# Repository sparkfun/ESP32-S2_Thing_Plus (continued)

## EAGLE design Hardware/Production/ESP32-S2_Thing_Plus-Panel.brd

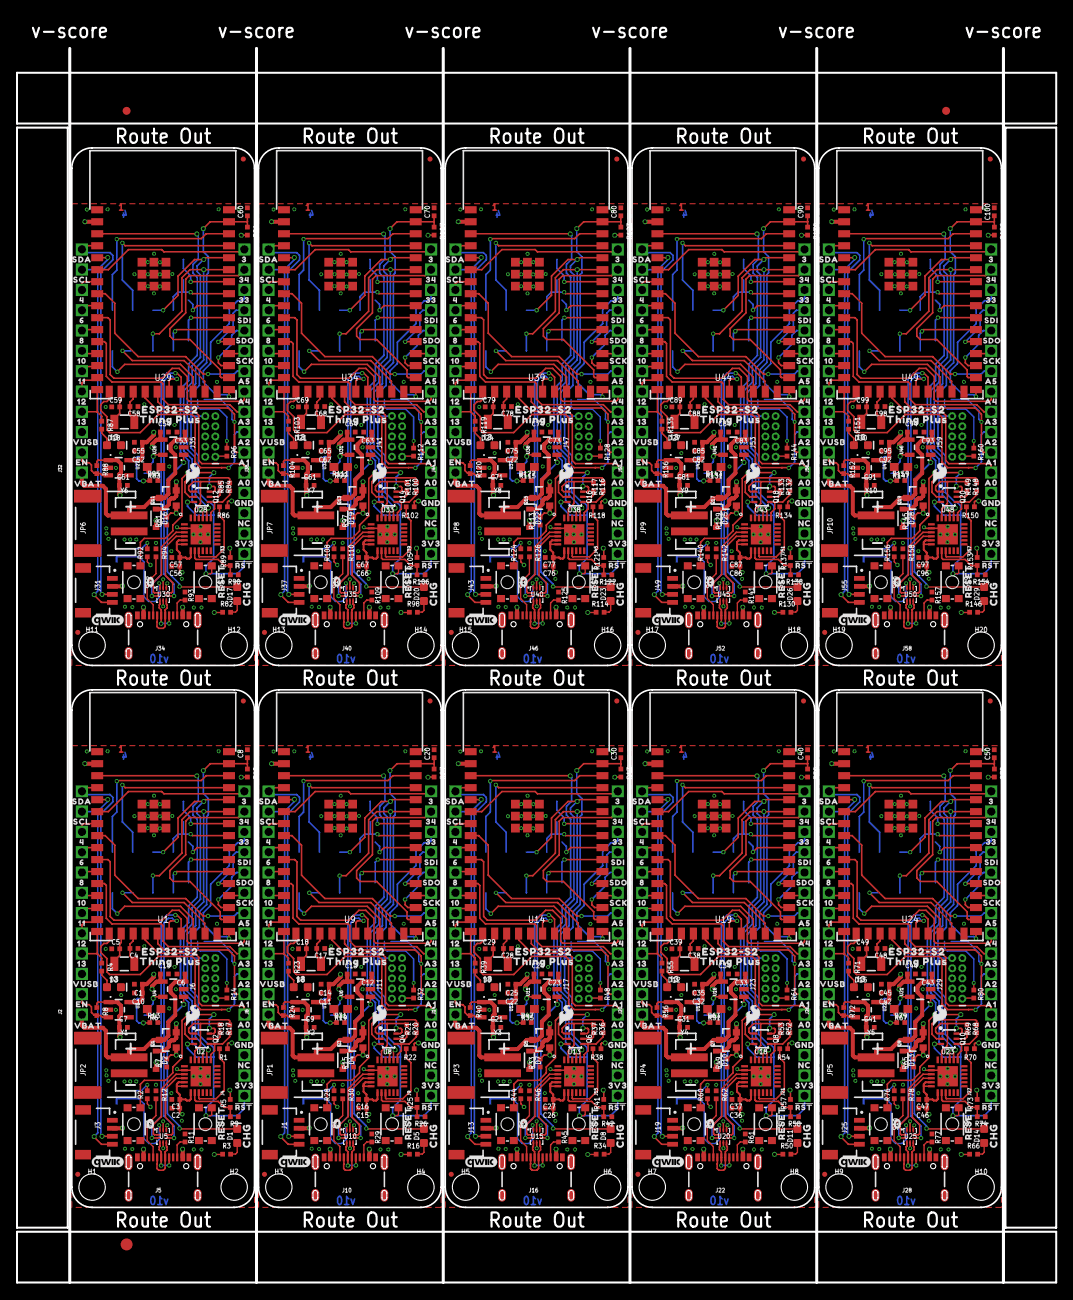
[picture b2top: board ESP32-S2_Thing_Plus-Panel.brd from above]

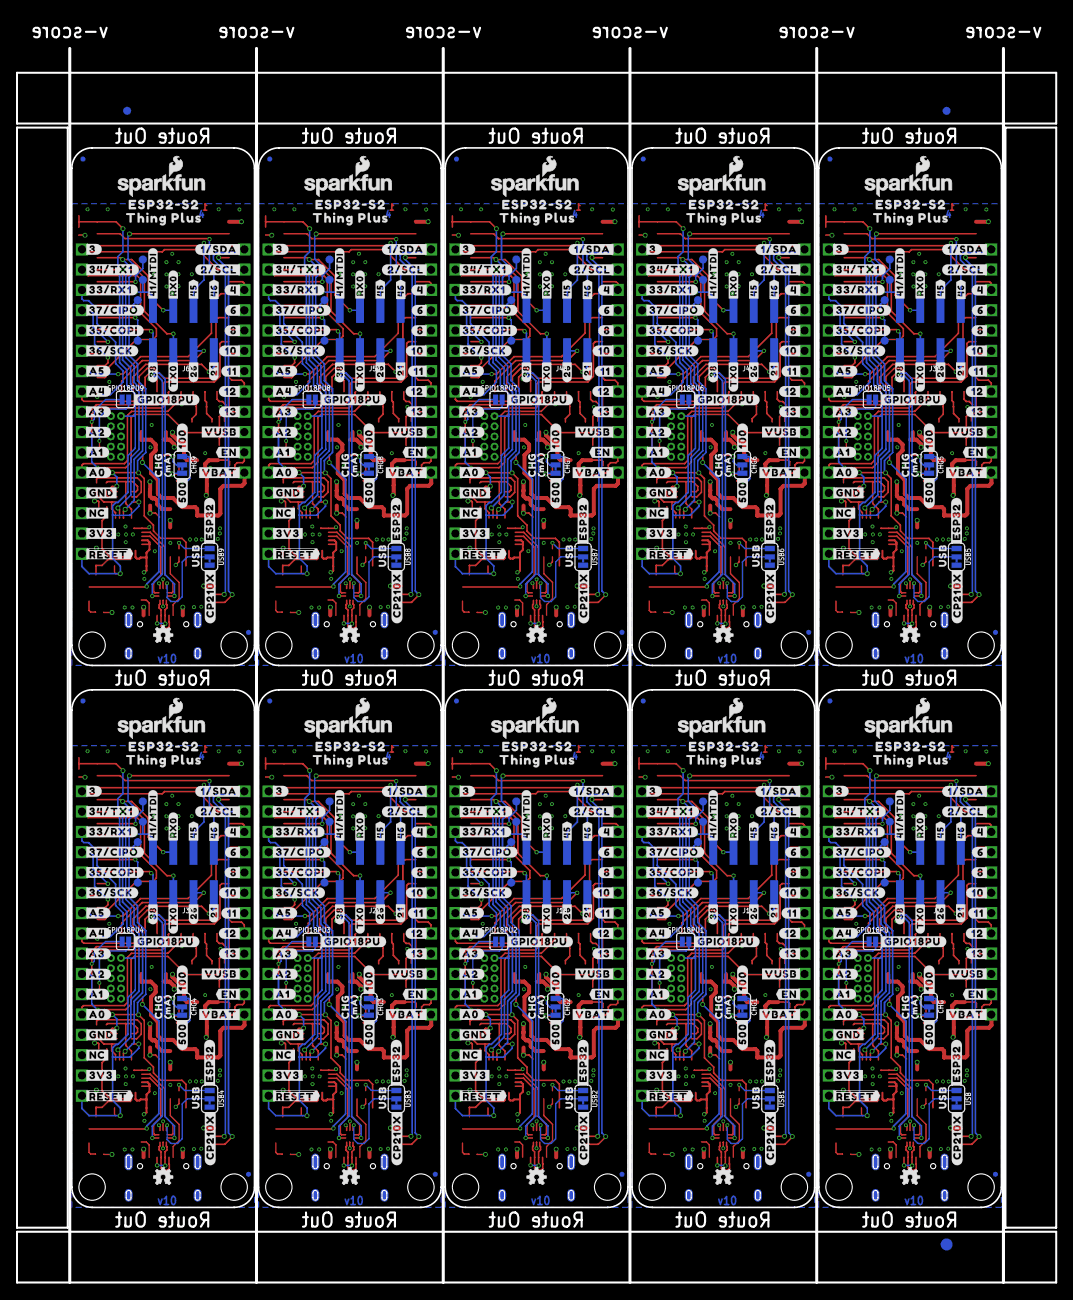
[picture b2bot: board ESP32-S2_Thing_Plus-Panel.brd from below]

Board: 4 copper layers, 130.0 x 154.4 mm, 1466 parts (583 on the bottom side), 650 nets.

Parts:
C1, C14, C25, C35, C45, C55, C65, C75, C85, C95: 10uF; 0402-TIGHT
C2, C8, C15, C20, C26, C30, C36, C40, C46, C50, C56, C60, C66, C70, C76, C80, C86, C90, C96, C100: 0.1uF; 0402-TIGHT
C3, C6, C12, C13, C16, C19, C23, C24, C27, C33, C34, C37, C43, C44, C47, C53, C54, C57, C63, C64, C67, C73, C74, C77, C83, C84, C87, C93, C94, C97: 4.7uF; 0402-TIGHT
C4, C5, C17, C18, C28, C29, C38, C39, C48, C49, C58, C59, C68, C69, C78, C79, C88, C89, C98, C99: 15pF; 0402-TIGHT
C7, C9, C10, C11, C21, C22, C31, C32, C41, C42, C51, C52, C61, C62, C71, C72, C81, C82, C91, C92: 1.0uF; 0402-TIGHT
CHG, CHG1, CHG2, CHG3, CHG4, CHG5, CHG6, CHG7, CHG8, CHG9: SMT-JUMPER_3_1-NC_TRACE_SILK
D1, D5, D8, D11, D14, D17, D20, D23, D26, D29: Yellow; LED-0603
D2, D4, D7, D10, D13, D16, D19, D22, D25, D28: 1A/23V/620mV; SOD-323
D3, D6, D9, D12, D15, D18, D21, D24, D27, D30: BLUE; LED-0603
E$1, E$2, E$3, E$4: FIDUCIAL-1X2
E$5, E$6: FIDUCIAL-1.5X3
FD1, FD2, FD3, FD4, FD5, FD6, FD7, FD8, FD9, FD10, FD11, FD12, FD13, FD14, FD15, FD16, FD17, FD18, FD19, FD20, FD21, FD22, FD23, FD24, FD25, FD26, FD27, FD28, FD29, FD30, FD31, FD32, FD33, FD34, FD35, FD36, FD37, FD38, FD39, FD40: FIDUCIALUFIDUCIAL; FIDUCIAL-MICRO
GPIO18PU, GPIO18PU1, GPIO18PU2, GPIO18PU3, GPIO18PU4, GPIO18PU5, GPIO18PU6, GPIO18PU7, GPIO18PU8, GPIO18PU9: SMT-JUMPER_2_NO_SILK
H1, H2, H3, H4, H5, H6, H7, H8, H9, H10, H11, H12, H13, H14, H15, H16, H17, H18, H19, H20: STAND-OFF
J1, J3, J13, J19, J25, J31, J37, J43, J49, J55: QWIIC_RA; JST04_1MM_RA
J2, J8, J14, J20, J26, J32, J38, J44, J50, J56: 1X12_SM_SQ_NOSILK
J4, J9, J15, J21, J27, J33, J39, J45, J51, J57: 1X16_SM_SQ_NOSILK
J5, J10, J16, J22, J28, J34, J40, J46, J52, J58: USB-C; USB-C-16P-4LAYER-ISOLATED
J6, J11, J17, J23, J29, J35, J41, J47, J53, J59: JTAG; 2X5-PTH-1.27MM-NO_SILK
J7, J12, J18, J24, J30, J36, J42, J48, J54, J60: 2X4_SMT_NO_POSTS_NS
JP1, JP2, JP3, JP4, JP5, JP6, JP7, JP8, JP9, JP10: LiPo; JST-2-SMD
LOGO1, LOGO10, LOGO15, LOGO20, LOGO25, LOGO30, LOGO35, LOGO40, LOGO45, LOGO50: SFE_LOGO_FLAME.1_INCH; SFE_LOGO_FLAME_.1
LOGO2, LOGO5, LOGO11, LOGO16, LOGO21, LOGO26, LOGO31, LOGO36, LOGO41, LOGO46: OSHW-LOGOMINI; OSHW-LOGO-MINI
LOGO3, LOGO7, LOGO12, LOGO17, LOGO22, LOGO27, LOGO32, LOGO37, LOGO42, LOGO47: SFE_LOGO_NAME_FLAME.1_INCH; SFE_LOGO_NAME_FLAME_.1
LOGO4, LOGO8, LOGO13, LOGO18, LOGO23, LOGO28, LOGO33, LOGO38, LOGO43, LOGO48: FOUR_LAYER_WARNING
LOGO6, LOGO9, LOGO14, LOGO19, LOGO24, LOGO29, LOGO34, LOGO39, LOGO44, LOGO49: QWIIC_LOGO_4MM; QWIIC_4MM
Q1, Q3, Q5, Q7, Q9, Q11, Q13, Q15, Q17, Q19: 2.5A/30V; SOT23-3@1
Q2, Q4, Q6, Q8, Q10, Q12, Q14, Q16, Q18, Q20: MBT3904DW1T1; SC70-6
R1, R2, R7, R10, R13, R14, R15, R17, R18, R20, R21, R22, R27, R28, R31, R32, R33, R36, R37, R38, R43, R44, R47, R48, R49, R52, R53, R54, R59, R60, R63, R64, R65, R68, R69, R70, R75, R76, R79, R80, R81, R84, R85, R86, R91, R92, R95, R96, R97, R100, R101, R102, R107, R108, R111, R112, R113, R116, R117, R118, R123, R124, R127, R128, R129, R132, R133, R134, R139, R140, R143, R144, R145, R148, R149, R150, R155, R156, R159, R160: 10k; 0402-TIGHT
R3, R4, R16, R23, R34, R39, R50, R55, R66, R71, R82, R87, R98, R103, R114, R119, R130, R135, R146, R151: 1k; 0402-TIGHT
R5, R25, R41, R57, R73, R89, R105, R121, R137, R153: 22k; 0402-TIGHT
R6, R19, R35, R51, R67, R83, R99, R115, R131, R147: 2.0k; 0603
R8, R24, R40, R56, R72, R88, R104, R120, R136, R152: 100k; 0402-TIGHT
R9, R26, R42, R58, R74, R90, R106, R122, R138, R154: 33k; 0402-TIGHT
R11, R12, R29, R30, R45, R46, R61, R62, R77, R78, R93, R94, R109, R110, R125, R126, R141, R142, R157, R158: 5.1k; 0402-TIGHT
S1, S3, S5, S7, S9, S11, S13, S15, S17, S19: RESET; TACTILE_SWITCH_SMD_4.6X2.8MM
S2, S4, S6, S8, S10, S12, S14, S16, S18, S20: 0; TACTILE_SWITCH_SMD_4.6X2.8MM
TP1, TP6, TP11, TP16, TP21, TP26, TP31, TP36, TP41, TP46: TP_15TH
TP2, TP3, TP4, TP5, TP7, TP8, TP9, TP10, TP12, TP13, TP14, TP15, TP17, TP18, TP19, TP20, TP22, TP23, TP24, TP25, TP27, TP28, TP29, TP30, TP32, TP33, TP34, TP35, TP37, TP38, TP39, TP40, TP42, TP43, TP44, TP45, TP47, TP48, TP49, TP50: PAD.03X.04
U1, U9, U14, U19, U24, U29, U34, U39, U44, U49: ESP32-S2-WROOM
U2, U8, U13, U18, U23, U28, U33, U38, U43, U48: CP210X; QFN24
U3, U7, U12, U17, U22, U27, U32, U37, U42, U47: AP2112; SOT23-5
U4, U6, U11, U16, U21, U26, U31, U36, U41, U46: MCP73831; SOT23-5
U5, U10, U15, U20, U25, U30, U35, U40, U45, U50: TC7USB40MU; UQFN10
U$1, U$160, U$241, U$322, U$403, U$484, U$565, U$646, U$727, U$808: #CP210X#0
U$2, U$116, U$197, U$278, U$359, U$440, U$521, U$602, U$683, U$764: SDI0
U$3, U$78, U$80, U$141, U$172, U$222, U$253, U$303, U$334, U$384, U$415, U$465, U$496, U$546, U$577, U$627, U$658, U$708, U$739, U$789: CHG0
U$4, U$152, U$233, U$314, U$395, U$476, U$557, U$638, U$719, U$800: #500#0
U$5, U$153, U$234, U$315, U$396, U$477, U$558, U$639, U$720, U$801: ESP32#S20
U$6, U$117, U$198, U$279, U$360, U$441, U$522, U$603, U$684, U$765: SDO0
U$7, U$118, U$199, U$280, U$361, U$442, U$523, U$604, U$685, U$766: #RST#0
U$8, U$142, U$223, U$304, U$385, U$466, U$547, U$628, U$709, U$790: #46#0
U$9, U$161, U$242, U$323, U$404, U$485, U$566, U$647, U$728, U$809: #ESP32#0
U$10, U$143, U$224, U$305, U$386, U$467, U$548, U$629, U$710, U$791: #45#0
U$11, U$150, U$231, U$312, U$393, U$474, U$555, U$636, U$717, U$798: MA0
U$12, U$109, U$190, U$271, U$352, U$433, U$514, U$595, U$676, U$757: #A5#0
U$13, U$59, U$163, U$244, U$325, U$406, U$487, U$568, U$649, U$730: ORDERING_INSTRUCTIONS
U$14, U$119, U$200, U$281, U$362, U$443, U$524, U$605, U$686, U$767: USB0
U$15, U$120, U$201, U$282, U$363, U$444, U$525, U$606, U$687, U$768: 110
U$16, U$162, U$243, U$324, U$405, U$486, U$567, U$648, U$729, U$810: #GPIO18PU#0
U$17, U$121, U$202, U$283, U$364, U$445, U$526, U$607, U$688, U$769: 100
U$18, U$122, U$203, U$284, U$365, U$446, U$527, U$608, U$689, U$770: 80
U$19, U$110, U$191, U$272, U$353, U$434, U$515, U$596, U$677, U$758: #A4#0
U$20, U$123, U$204, U$285, U$366, U$447, U$528, U$609, U$690, U$771: 60
U$21, U$158, U$239, U$320, U$401, U$482, U$563, U$644, U$725, U$806: #A2#0
U$22, U$159, U$240, U$321, U$402, U$483, U$564, U$645, U$726, U$807: #A3#0
U$23, U$124, U$205, U$286, U$367, U$448, U$529, U$610, U$691, U$772: 40
U$24, U$125, U$206, U$287, U$368, U$449, U$530, U$611, U$692, U$773: 330
U$25, U$27, U$164, U$245, U$326, U$407, U$488, U$569, U$650, U$731: SDA0
U$26, U$65, U$165, U$246, U$327, U$408, U$489, U$570, U$651, U$732: SCL0
U$28, U$111, U$192, U$273, U$354, U$435, U$516, U$597, U$678, U$759: #A0#0
U$29, U$126, U$207, U$288, U$369, U$450, U$531, U$612, U$693, U$774: 340
U$30, U$127, U$208, U$289, U$370, U$451, U$532, U$613, U$694, U$775: 30
U$31, U$135, U$216, U$297, U$378, U$459, U$540, U$621, U$702, U$783: #36#SCK#0
U$32, U$112, U$193, U$274, U$355, U$436, U$517, U$598, U$679, U$760: #GND#0
U$33, U$136, U$217, U$298, U$379, U$460, U$541, U$622, U$703, U$784: #35#COPI#0
U$34, U$137, U$218, U$299, U$380, U$461, U$542, U$623, U$704, U$785: #37#CIPO#0
U$35, U$138, U$219, U$300, U$381, U$462, U$543, U$624, U$705, U$786: #33#RX1#0
U$36, U$139, U$220, U$301, U$382, U$463, U$544, U$625, U$706, U$787: #34#TX1#0
U$37, U$140, U$221, U$302, U$383, U$464, U$545, U$626, U$707, U$788: #3#0
U$38, U$144, U$225, U$306, U$387, U$468, U$549, U$630, U$711, U$792: #41#MTDI#0
U$39, U$104, U$185, U$266, U$347, U$428, U$509, U$590, U$671, U$752: #12#0
U$40, U$105, U$186, U$267, U$348, U$429, U$510, U$591, U$672, U$753: #13#0
U$41, U$106, U$187, U$268, U$349, U$430, U$511, U$592, U$673, U$754: #VUSB#0
U$42, U$107, U$188, U$269, U$350, U$431, U$512, U$593, U$674, U$755: #VBAT#0
U$43, U$108, U$189, U$270, U$351, U$432, U$513, U$594, U$675, U$756: #EN#0
U$44, U$113, U$194, U$275, U$356, U$437, U$518, U$599, U$680, U$761: #NC#0
U$45, U$114, U$195, U$276, U$357, U$438, U$519, U$600, U$681, U$762: #3V3#0
U$46, U$115, U$196, U$277, U$358, U$439, U$520, U$601, U$682, U$763: ##RESET##0
U$47, U$128, U$209, U$290, U$371, U$452, U$533, U$614, U$695, U$776: #11#0
U$48, U$131, U$212, U$293, U$374, U$455, U$536, U$617, U$698, U$779: #6#0
U$49, U$129, U$210, U$291, U$372, U$453, U$534, U$615, U$696, U$777: #8#0
U$50, U$130, U$211, U$292, U$373, U$454, U$535, U$616, U$697, U$778: #10#0
U$51, U$132, U$213, U$294, U$375, U$456, U$537, U$618, U$699, U$780: #4#0
U$52, U$133, U$214, U$295, U$376, U$457, U$538, U$619, U$700, U$781: #1#SDA#0
U$53, U$134, U$215, U$296, U$377, U$458, U$539, U$620, U$701, U$782: #2#SCL#0
U$54, U$145, U$226, U$307, U$388, U$469, U$550, U$631, U$712, U$793: #21#0
U$55, U$146, U$227, U$308, U$389, U$470, U$551, U$632, U$713, U$794: #26#0
U$56, U$147, U$228, U$309, U$390, U$471, U$552, U$633, U$714, U$795: #TX0#0
U$57, U$148, U$229, U$310, U$391, U$472, U$553, U$634, U$715, U$796: #38#0
U$58, U$149, U$230, U$311, U$392, U$473, U$554, U$635, U$716, U$797: #RX0#0
U$60, U$151, U$232, U$313, U$394, U$475, U$556, U$637, U$718, U$799: #100#0
U$61, U$154, U$235, U$316, U$397, U$478, U$559, U$640, U$721, U$802: THING_PLUS0
U$62, U$155, U$236, U$317, U$398, U$479, U$560, U$641, U$722, U$803: THING_PLUS_0
U$63, U$156, U$237, U$318, U$399, U$480, U$561, U$642, U$723, U$804: ESP32#S2_0
U$64, U$157, U$238, U$319, U$400, U$481, U$562, U$643, U$724, U$805: #A1#0
U$66, U$72, U$166, U$247, U$328, U$409, U$490, U$571, U$652, U$733: 120
U$67, U$68, U$73, U$74, U$167, U$168, U$248, U$249, U$329, U$330, U$410, U$411, U$491, U$492, U$572, U$573, U$653, U$654, U$734, U$735: 130
U$69, U$75, U$169, U$250, U$331, U$412, U$493, U$574, U$655, U$736: VUSB0
U$70, U$76, U$170, U$251, U$332, U$413, U$494, U$575, U$656, U$737: EN0
U$71, U$77, U$171, U$252, U$333, U$414, U$495, U$576, U$657, U$738: VBAT0
U$79, U$91, U$173, U$254, U$335, U$416, U$497, U$578, U$659, U$740: RESET0
U$81, U$92, U$174, U$255, U$336, U$417, U$498, U$579, U$660, U$741: 3V30
U$82, U$93, U$175, U$256, U$337, U$418, U$499, U$580, U$661, U$742: NC0
U$83, U$94, U$176, U$257, U$338, U$419, U$500, U$581, U$662, U$743: GND0
U$84, U$95, U$177, U$258, U$339, U$420, U$501, U$582, U$663, U$744: A00
U$85, U$97, U$178, U$259, U$340, U$421, U$502, U$583, U$664, U$745: A10
U$86, U$98, U$179, U$260, U$341, U$422, U$503, U$584, U$665, U$746: A20
U$87, U$99, U$180, U$261, U$342, U$423, U$504, U$585, U$666, U$747: A30
U$88, U$100, U$181, U$262, U$343, U$424, U$505, U$586, U$667, U$748: A40
U$89, U$101, U$182, U$263, U$344, U$425, U$506, U$587, U$668, U$749: A50
U$90, U$102, U$183, U$264, U$345, U$426, U$507, U$588, U$669, U$750: SCK0
U$96, U$103, U$184, U$265, U$346, U$427, U$508, U$589, U$670, U$751: 00
USB, USB1, USB2, USB3, USB4, USB5, USB6, USB7, USB8, USB9: SMT-JUMPER_3_1-NC_TRACE_SILK
Y1, Y2, Y3, Y4, Y5, Y6, Y7, Y8, Y9, Y10: 32.768kHz; CRYSTAL-SMD-3.2X1.5MM

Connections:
0: Q2.6, S2.4, TP1.P$1, U1.3
1: Q4.6, S4.4, TP6.P$1, U9.3
2: J8.4, R23.1, U9.16
3: J4.16, U1.6
3.3V: C1.1, C2.1, C3.1, C10.1, J3.2, J4.2, J6.1, R1.1, R2.1, R10.2, R14.2, U1.2, U2.5, U2.6, U2.7, U3.5, U5.9
3.3V1: C11.1, C14.1, C15.1, C16.1, J1.2, J9.2, J11.1, R22.1, R27.2, R28.1, R32.2, U7.5, U8.5, U8.6, U8.7, U9.2, U10.9
3.3V2: C22.1, C25.1, C26.1, C27.1, J13.2, J15.2, J17.1, R38.1, R43.2, R44.1, R48.2, U12.5, U13.5, U13.6, U13.7, U14.2, U15.9
3.3V3: C32.1, C35.1, C36.1, C37.1, J19.2, J21.2, J23.1, R54.1, R59.2, R60.1, R64.2, U17.5, U18.5, U18.6, U18.7, U19.2, U20.9
3.3V4: C42.1, C45.1, C46.1, C47.1, J25.2, J27.2, J29.1, R70.1, R75.2, R76.1, R80.2, U22.5, U23.5, U23.6, U23.7, U24.2, U25.9
3.3V5: C52.1, C55.1, C56.1, C57.1, J31.2, J33.2, J35.1, R86.1, R91.2, R92.1, R96.2, U27.5, U28.5, U28.6, U28.7, U29.2, U30.9
3.3V6: C62.1, C65.1, C66.1, C67.1, J37.2, J39.2, J41.1, R102.1, R107.2, R108.1, R112.2, U32.5, U33.5, U33.6, U33.7, U34.2, U35.9
3.3V7: C72.1, C75.1, C76.1, C77.1, J43.2, J45.2, J47.1, R118.1, R123.2, R124.1, R128.2, U37.5, U38.5, U38.6, U38.7, U39.2, U40.9
3.3V8: C82.1, C85.1, C86.1, C87.1, J49.2, J51.2, J53.1, R134.1, R139.2, R140.1, R144.2, U42.5, U43.5, U43.6, U43.7, U44.2, U45.9
3.3V9: C92.1, C95.1, C96.1, C97.1, J55.2, J57.2, J59.1, R150.1, R155.2, R156.1, R160.2, U47.5, U48.5, U48.6, U48.7, U49.2, U50.9
4: J2.10, U1.7
5: J8.5, U9.15
6: J2.9, U1.9
7: J8.6, U9.14
8: J2.8, U1.11
9: J8.7, U9.13
10: J2.7, U1.13
11: J2.6, U1.14
12: J2.5, U1.15
13: J2.4, R4.1, U1.16
14: J8.8, U9.11
15: J8.9, U9.9
16: J8.10, U9.7
17: J9.16, U9.6
18: J12.3, U9.39
19: J12.1, U9.40
20: J12.8, U9.32
21: J7.2, U1.24
22: J12.2, U9.24
23: J12.4, U9.25
24: Q6.6, S6.4, TP11.P$1, U14.3
25: J14.4, R39.1, U14.16
26: J7.4, U1.25
27: J14.5, U14.15
28: J14.6, U14.14
29: J14.7, U14.13
30: J14.8, U14.11
31: J14.9, U14.9
32: J14.10, U14.7
33: J15.16, U14.6
33/RX1: J4.14, U1.27
33/RX2: J9.14, U9.27
33/RX3: J15.14, U14.27
33/RX4: J21.14, U19.27
33/RX5: J27.14, U24.27
33/RX6: J33.14, U29.27
33/RX7: J39.14, U34.27
33/RX8: J45.14, U39.27
33/RX9: J51.14, U44.27
33/RX10: J57.14, U49.27
34: J18.3, U14.39
34/TX1: J4.15, U1.28
34/TX2: J9.15, U9.28
34/TX3: J15.15, U14.28
34/TX4: J21.15, U19.28
34/TX5: J27.15, U24.28
34/TX6: J33.15, U29.28
34/TX7: J39.15, U34.28
34/TX8: J45.15, U39.28
34/TX9: J51.15, U44.28
34/TX10: J57.15, U49.28
35: J18.1, U14.40
36: J18.8, U14.32
37: J18.2, U14.24
38: J7.8, U1.32
39: J18.4, U14.25
40: Q8.6, S8.4, TP16.P$1, U19.3
41: J20.4, R55.1, U19.16
41/MTDI: J6.8, J7.7, TP2.P$1, U1.35
41/MTDI1: J11.8, J12.7, TP10.P$1, U9.35
41/MTDI2: J17.8, J18.7, TP15.P$1, U14.35
41/MTDI3: J23.8, J24.7, TP20.P$1, U19.35
41/MTDI4: J29.8, J30.7, TP25.P$1, U24.35
41/MTDI5: J35.8, J36.7, TP30.P$1, U29.35
41/MTDI6: J41.8, J42.7, TP35.P$1, U34.35
41/MTDI7: J47.8, J48.7, TP40.P$1, U39.35
41/MTDI8: J53.8, J54.7, TP45.P$1, U44.35
41/MTDI9: J59.8, J60.7, TP50.P$1, U49.35
42: J20.5, U19.15
43: J20.6, U19.14
44: J20.7, U19.13
45: J7.3, U1.39
46: J7.1, U1.40
47: J20.8, U19.11
48: J20.9, U19.9
49: J20.10, U19.7
50: J21.16, U19.6
51: J24.3, U19.39
52: J24.1, U19.40
53: J24.8, U19.32
54: J24.2, U19.24
55: J24.4, U19.25
56: Q10.6, S10.4, TP21.P$1, U24.3
57: J26.4, R71.1, U24.16
58: J26.5, U24.15
59: J26.6, U24.14
60: J26.7, U24.13
61: J26.8, U24.11
62: J26.9, U24.9
63: J26.10, U24.7
64: J27.16, U24.6
65: J30.3, U24.39
66: J30.1, U24.40
67: J30.8, U24.32
68: J30.2, U24.24
69: J30.4, U24.25
70: Q12.6, S12.4, TP26.P$1, U29.3
71: J32.4, R87.1, U29.16
72: J32.5, U29.15
73: J32.6, U29.14
74: J32.7, U29.13
75: J32.8, U29.11
76: J32.9, U29.9
77: J32.10, U29.7
78: J33.16, U29.6
79: J36.3, U29.39
80: J36.1, U29.40
81: J36.8, U29.32
82: J36.2, U29.24
83: J36.4, U29.25
84: Q14.6, S14.4, TP31.P$1, U34.3
85: J38.4, R103.1, U34.16
86: J38.5, U34.15
87: J38.6, U34.14
88: J38.7, U34.13
89: J38.8, U34.11
90: J38.9, U34.9
91: J38.10, U34.7
92: J39.16, U34.6
93: J42.3, U34.39
94: J42.1, U34.40
95: J42.8, U34.32
96: J42.2, U34.24
97: J42.4, U34.25
98: Q16.6, S16.4, TP36.P$1, U39.3
99: J44.4, R119.1, U39.16
100: J44.5, U39.15
101: J44.6, U39.14
102: J44.7, U39.13
103: J44.8, U39.11
104: J44.9, U39.9
105: J44.10, U39.7
106: J45.16, U39.6
107: J48.3, U39.39
108: J48.1, U39.40
109: J48.8, U39.32
110: J48.2, U39.24
111: J48.4, U39.25
112: Q18.6, S18.4, TP41.P$1, U44.3
113: J50.4, R135.1, U44.16
114: J50.5, U44.15
115: J50.6, U44.14
116: J50.7, U44.13
117: J50.8, U44.11
118: J50.9, U44.9
119: J50.10, U44.7
120: J51.16, U44.6
121: J54.3, U44.39
122: J54.1, U44.40
123: J54.8, U44.32
124: J54.2, U44.24
125: J54.4, U44.25
126: Q20.6, S20.4, TP46.P$1, U49.3
127: J56.4, R151.1, U49.16
128: J56.5, U49.15
129: J56.6, U49.14
130: J56.7, U49.13
131: J56.8, U49.11
132: J56.9, U49.9
133: J56.10, U49.7
134: J57.16, U49.6
135: J60.3, U49.39
136: J60.1, U49.40
137: J60.8, U49.32
138: J60.2, U49.24
139: J60.4, U49.25
A0: J4.5, U1.20
A1: GPIO18PU.1, J4.6, U1.21
A2: J4.7, U1.17
A3: J4.8, U1.12
A4: J4.9, U1.10
A5: J4.10, U1.8
A6: J9.5, U9.20
A7: GPIO18PU1.1, J9.6, U9.21
A8: J9.7, U9.17
A9: J9.8, U9.12
A10: J9.9, U9.10
A11: J9.10, U9.8
A12: J15.5, U14.20
A13: GPIO18PU2.1, J15.6, U14.21
A14: J15.7, U14.17
A15: J15.8, U14.12
A16: J15.9, U14.10
A17: J15.10, U14.8
A18: J21.5, U19.20
A19: GPIO18PU3.1, J21.6, U19.21
A20: J21.7, U19.17
A21: J21.8, U19.12
A22: J21.9, U19.10
A23: J21.10, U19.8
A24: J27.5, U24.20
A25: GPIO18PU4.1, J27.6, U24.21
A26: J27.7, U24.17
A27: J27.8, U24.12
A28: J27.9, U24.10
A29: J27.10, U24.8
A30: J33.5, U29.20
A31: GPIO18PU5.1, J33.6, U29.21
A32: J33.7, U29.17
A33: J33.8, U29.12
A34: J33.9, U29.10
A35: J33.10, U29.8
A36: J39.5, U34.20
A37: GPIO18PU6.1, J39.6, U34.21
A38: J39.7, U34.17
A39: J39.8, U34.12
A40: J39.9, U34.10
A41: J39.10, U34.8
A42: J45.5, U39.20
A43: GPIO18PU7.1, J45.6, U39.21
A44: J45.7, U39.17
A45: J45.8, U39.12
A46: J45.9, U39.10
A47: J45.10, U39.8
A48: J51.5, U44.20
A49: GPIO18PU8.1, J51.6, U44.21
A50: J51.7, U44.17
A51: J51.8, U44.12
A52: J51.9, U44.10
A53: J51.10, U44.8
A54: J57.5, U49.20
A55: GPIO18PU9.1, J57.6, U49.21
A56: J57.7, U49.17
A57: J57.8, U49.12
A58: J57.9, U49.10
A59: J57.10, U49.8
CC1: J5.A5, R12.2
CC2: J5.B5, R11.2
CC3: J10.B5, R29.2
CC4: J10.A5, R30.2
CC5: J16.B5, R45.2
CC6: J16.A5, R46.2
CC7: J22.B5, R61.2
CC8: J22.A5, R62.2
CC9: J28.B5, R77.2
CC10: J28.A5, R78.2
CC11: J34.B5, R93.2
CC12: J34.A5, R94.2
CC13: J40.B5, R109.2
CC14: J40.A5, R110.2
CC15: J46.B5, R125.2
CC16: J46.A5, R126.2
CC17: J52.B5, R141.2
CC18: J52.A5, R142.2
CC19: J58.B5, R157.2
CC20: J58.A5, R158.2
CHG: D1.C, U4.1
CHG1: D5.C, U6.1
CHG2: D8.C, U11.1
CHG3: D11.C, U16.1
CHG4: D14.C, U21.1
CHG5: D17.C, U26.1
CHG6: D20.C, U31.1
CHG7: D23.C, U36.1
CHG8: D26.C, U41.1
CHG9: D29.C, U46.1
CHIP_PU: C8.1, J4.1, J6.10, Q2.3, R10.1, S1.4, U1.41
CHIP_PU1: C20.1, J9.1, J11.10, Q4.3, R27.1, S3.4, U9.41
CHIP_PU2: C30.1, J15.1, J17.10, Q6.3, R43.1, S5.4, U14.41
CHIP_PU3: C40.1, J21.1, J23.10, Q8.3, R59.1, S7.4, U19.41
CHIP_PU4: C50.1, J27.1, J29.10, Q10.3, R75.1, S9.4, U24.41
CHIP_PU5: C60.1, J33.1, J35.10, Q12.3, R91.1, S11.4, U29.41
CHIP_PU6: C70.1, J39.1, J41.10, Q14.3, R107.1, S13.4, U34.41
CHIP_PU7: C80.1, J45.1, J47.10, Q16.3, R123.1, S15.4, U39.41
CHIP_PU8: C90.1, J51.1, J53.10, Q18.3, R139.1, S17.4, U44.41
CHIP_PU9: C100.1, J57.1, J59.10, Q20.3, R155.1, S19.4, U49.41
CIPO: J4.13, U1.31
CIPO1: J9.13, U9.31
CIPO2: J15.13, U14.31
CIPO3: J21.13, U19.31
CIPO4: J27.13, U24.31
CIPO5: J33.13, U29.31
CIPO6: J39.13, U34.31
CIPO7: J45.13, U39.31
CIPO8: J51.13, U44.31
CIPO9: J57.13, U49.31
COPI: J4.12, U1.29
COPI1: J9.12, U9.29
COPI2: J15.12, U14.29
COPI3: J21.12, U19.29
COPI4: J27.12, U24.29
COPI5: J33.12, U29.29
COPI6: J39.12, U34.29
COPI7: J45.12, U39.29
COPI8: J51.12, U44.29
COPI9: J57.12, U49.29
CP210X_D+: U2.3, U5.1
CP210X_D+1: U8.3, U10.1
CP210X_D+2: U13.3, U15.1
CP210X_D+3: U18.3, U20.1
CP210X_D+4: U23.3, U25.1
CP210X_D+5: U28.3, U30.1
CP210X_D+6: U33.3, U35.1
CP210X_D+7: U38.3, U40.1
CP210X_D+8: U43.3, U45.1
CP210X_D+9: U48.3, U50.1
CP210X_D-: U2.4, U5.7
CP210X_D-1: U8.4, U10.7
CP210X_D-2: U13.4, U15.7
CP210X_D-3: U18.4, U20.7
CP210X_D-4: U23.4, U25.7
CP210X_D-5: U28.4, U30.7
CP210X_D-6: U33.4, U35.7
CP210X_D-7: U38.4, U40.7
CP210X_D-8: U43.4, U45.7
CP210X_D-9: U48.4, U50.7
DTR: Q2.1, R17.1, U2.23
DTR1: Q4.1, R20.1, U8.23
DTR2: Q6.1, R36.1, U13.23
DTR3: Q8.1, R52.1, U18.23
DTR4: Q10.1, R68.1, U23.23
DTR5: Q12.1, R84.1, U28.23
DTR6: Q14.1, R100.1, U33.23
DTR7: Q16.1, R116.1, U38.23
DTR8: Q18.1, R132.1, U43.23
DTR9: Q20.1, R148.1, U48.23
EN: J2.2, R8.2, U3.3
EN1: J8.2, R24.2, U7.3
EN2: J14.2, R40.2, U12.3
EN3: J20.2, R56.2, U17.3
EN4: J26.2, R72.2, U22.3
EN5: J32.2, R88.2, U27.3
EN6: J38.2, R104.2, U32.3
EN7: J44.2, R120.2, U37.3
EN8: J50.2, R136.2, U42.3
EN9: J56.2, R152.2, U47.3
ESP32_D+: U1.23, U5.2
ESP32_D+1: U9.23, U10.2
ESP32_D+2: U14.23, U15.2
ESP32_D+3: U19.23, U20.2
ESP32_D+4: U24.23, U25.2
ESP32_D+5: U29.23, U30.2
ESP32_D+6: U34.23, U35.2
ESP32_D+7: U39.23, U40.2
ESP32_D+8: U44.23, U45.2
ESP32_D+9: U49.23, U50.2
ESP32_D-: U1.22, U5.6
ESP32_D-1: U9.22, U10.6
ESP32_D-2: U14.22, U15.6
ESP32_D-3: U19.22, U20.6
ESP32_D-4: U24.22, U25.6
ESP32_D-5: U29.22, U30.6
ESP32_D-6: U34.22, U35.6
ESP32_D-7: U39.22, U40.6
ESP32_D-8: U44.22, U45.6
ESP32_D-9: U49.22, U50.6
GND: C1.2, C2.2, C3.2, C4.1, C5.1, C6.2, C7.2, C8.2, C10.2, C19.2, D3.C, J3.1, J4.4, J5.GND, J5.GND2, J6.3, J6.5, J6.7, J6.9, JP2.1, R6.1, R7.1, R9.1, R11.1, R12.1, R13.2, S1.1, S2.1, U1.1, U1.26, U1.42, U1.GNDEP0, U1.GNDEP1, U1.GNDEP2, U1.GNDEP3, U1.GNDEP4, U1.GNDEP5, U1.GNDEP6, U1.GNDEP7, U1.GNDEP8, U2.2, U2.PAD, U3.2, U4.2, U5.4, U5.8, USB.3
GND1: C9.2, C11.2, C12.2, C13.2, C14.2, C15.2, C16.2, C17.1, C18.1, C20.2, D6.C, J1.1, J9.4, J10.GND, J10.GND2, J11.3, J11.5, J11.7, J11.9, JP1.1, R15.1, R19.1, R26.1, R29.1, R30.1, R31.2, S3.1, S4.1, U6.2, U7.2, U8.2, U8.PAD, U9.1, U9.26, U9.42, U9.GNDEP0, U9.GNDEP1, U9.GNDEP2, U9.GNDEP3, U9.GNDEP4, U9.GNDEP5, U9.GNDEP6, U9.GNDEP7, U9.GNDEP8, U10.4, U10.8, USB1.3
GND2: C21.2, C22.2, C23.2, C24.2, C25.2, C26.2, C27.2, C28.1, C29.1, C30.2, D9.C, J13.1, J15.4, J16.GND, J16.GND2, J17.3, J17.5, J17.7, J17.9, JP3.1, R33.1, R35.1, R42.1, R45.1, R46.1, R47.2, S5.1, S6.1, U11.2, U12.2, U13.2, U13.PAD, U14.1, U14.26, U14.42, U14.GNDEP0, U14.GNDEP1, U14.GNDEP2, U14.GNDEP3, U14.GNDEP4, U14.GNDEP5, U14.GNDEP6, U14.GNDEP7, U14.GNDEP8, U15.4, U15.8, USB2.3
GND3: C31.2, C32.2, C33.2, C34.2, C35.2, C36.2, C37.2, C38.1, C39.1, C40.2, D12.C, J19.1, J21.4, J22.GND, J22.GND2, J23.3, J23.5, J23.7, J23.9, JP4.1, R49.1, R51.1, R58.1, R61.1, R62.1, R63.2, S7.1, S8.1, U16.2, U17.2, U18.2, U18.PAD, U19.1, U19.26, U19.42, U19.GNDEP0, U19.GNDEP1, U19.GNDEP2, U19.GNDEP3, U19.GNDEP4, U19.GNDEP5, U19.GNDEP6, U19.GNDEP7, U19.GNDEP8, U20.4, U20.8, USB3.3
GND4: C41.2, C42.2, C43.2, C44.2, C45.2, C46.2, C47.2, C48.1, C49.1, C50.2, D15.C, J25.1, J27.4, J28.GND, J28.GND2, J29.3, J29.5, J29.7, J29.9, JP5.1, R65.1, R67.1, R74.1, R77.1, R78.1, R79.2, S9.1, S10.1, U21.2, U22.2, U23.2, U23.PAD, U24.1, U24.26, U24.42, U24.GNDEP0, U24.GNDEP1, U24.GNDEP2, U24.GNDEP3, U24.GNDEP4, U24.GNDEP5, U24.GNDEP6, U24.GNDEP7, U24.GNDEP8, U25.4, U25.8, USB4.3
GND5: C51.2, C52.2, C53.2, C54.2, C55.2, C56.2, C57.2, C58.1, C59.1, C60.2, D18.C, J31.1, J33.4, J34.GND, J34.GND2, J35.3, J35.5, J35.7, J35.9, JP6.1, R81.1, R83.1, R90.1, R93.1, R94.1, R95.2, S11.1, S12.1, U26.2, U27.2, U28.2, U28.PAD, U29.1, U29.26, U29.42, U29.GNDEP0, U29.GNDEP1, U29.GNDEP2, U29.GNDEP3, U29.GNDEP4, U29.GNDEP5, U29.GNDEP6, U29.GNDEP7, U29.GNDEP8, U30.4, U30.8, USB5.3
GND6: C61.2, C62.2, C63.2, C64.2, C65.2, C66.2, C67.2, C68.1, C69.1, C70.2, D21.C, J37.1, J39.4, J40.GND, J40.GND2, J41.3, J41.5, J41.7, J41.9, JP7.1, R97.1, R99.1, R106.1, R109.1, R110.1, R111.2, S13.1, S14.1, U31.2, U32.2, U33.2, U33.PAD, U34.1, U34.26, U34.42, U34.GNDEP0, U34.GNDEP1, U34.GNDEP2, U34.GNDEP3, U34.GNDEP4, U34.GNDEP5, U34.GNDEP6, U34.GNDEP7, U34.GNDEP8, U35.4, U35.8, USB6.3
GND7: C71.2, C72.2, C73.2, C74.2, C75.2, C76.2, C77.2, C78.1, C79.1, C80.2, D24.C, J43.1, J45.4, J46.GND, J46.GND2, J47.3, J47.5, J47.7, J47.9, JP8.1, R113.1, R115.1, R122.1, R125.1, R126.1, R127.2, S15.1, S16.1, U36.2, U37.2, U38.2, U38.PAD, U39.1, U39.26, U39.42, U39.GNDEP0, U39.GNDEP1, U39.GNDEP2, U39.GNDEP3, U39.GNDEP4, U39.GNDEP5, U39.GNDEP6, U39.GNDEP7, U39.GNDEP8, U40.4, U40.8, USB7.3
GND8: C81.2, C82.2, C83.2, C84.2, C85.2, C86.2, C87.2, C88.1, C89.1, C90.2, D27.C, J49.1, J51.4, J52.GND, J52.GND2, J53.3, J53.5, J53.7, J53.9, JP9.1, R129.1, R131.1, R138.1, R141.1, R142.1, R143.2, S17.1, S18.1, U41.2, U42.2, U43.2, U43.PAD, U44.1, U44.26, U44.42, U44.GNDEP0, U44.GNDEP1, U44.GNDEP2, U44.GNDEP3, U44.GNDEP4, U44.GNDEP5, U44.GNDEP6, U44.GNDEP7, U44.GNDEP8, U45.4, U45.8, USB8.3
GND9: C91.2, C92.2, C93.2, C94.2, C95.2, C96.2, C97.2, C98.1, C99.1, C100.2, D30.C, J55.1, J57.4, J58.GND, J58.GND2, J59.3, J59.5, J59.7, J59.9, JP10.1, R145.1, R147.1, R154.1, R157.1, R158.1, R159.2, S19.1, S20.1, U46.2, U47.2, U48.2, U48.PAD, U49.1, U49.26, U49.42, U49.GNDEP0, U49.GNDEP1, U49.GNDEP2, U49.GNDEP3, U49.GNDEP4, U49.GNDEP5, U49.GNDEP6, U49.GNDEP7, U49.GNDEP8, U50.4, U50.8, USB9.3
MTCK: J6.4, TP4.P$1, U1.33
MTCK1: J11.4, TP8.P$1, U9.33
MTCK2: J17.4, TP13.P$1, U14.33
MTCK3: J23.4, TP18.P$1, U19.33
MTCK4: J29.4, TP23.P$1, U24.33
MTCK5: J35.4, TP28.P$1, U29.33
MTCK6: J41.4, TP33.P$1, U34.33
MTCK7: J47.4, TP38.P$1, U39.33
MTCK8: J53.4, TP43.P$1, U44.33
MTCK9: J59.4, TP48.P$1, U49.33
MTDO: J6.6, TP3.P$1, U1.34
MTDO1: J11.6, TP7.P$1, U9.34
MTDO2: J17.6, TP12.P$1, U14.34
MTDO3: J23.6, TP17.P$1, U19.34
MTDO4: J29.6, TP22.P$1, U24.34
MTDO5: J35.6, TP27.P$1, U29.34
MTDO6: J41.6, TP32.P$1, U34.34
MTDO7: J47.6, TP37.P$1, U39.34
MTDO8: J53.6, TP42.P$1, U44.34
MTDO9: J59.6, TP47.P$1, U49.34
MTMS: J6.2, TP5.P$1, U1.36
MTMS1: J11.2, TP9.P$1, U9.36
MTMS2: J17.2, TP14.P$1, U14.36
MTMS3: J23.2, TP19.P$1, U19.36
MTMS4: J29.2, TP24.P$1, U24.36
MTMS5: J35.2, TP29.P$1, U29.36
MTMS6: J41.2, TP34.P$1, U34.36
MTMS7: J47.2, TP39.P$1, U39.36
MTMS8: J53.2, TP44.P$1, U44.36
MTMS9: J59.2, TP49.P$1, U49.36
unnamed: R1.2, U2.9
unnamed: D3.A, R4.2
unnamed: J5.A6, J5.B6, U5.3
unnamed: R5.1, R9.2, U2.8
unnamed: J5.A7, J5.B7, U5.5
unnamed: R2.2, USB.1
unnamed: C5.2, U1.18, Y1.P$2
unnamed: C4.2, U1.19, Y1.P$1
unnamed: CHG.2, U4.5
unnamed: Q2.5, R17.2
unnamed: CHG.1, R13.1
unnamed: Q2.2, R18.2
unnamed: CHG.3, R6.2
unnamed: GPIO18PU.2, R14.1
unnamed: Q4.5, R20.2
unnamed: Q4.2, R21.2
unnamed: D1.A, R3.2
unnamed: D5.A, R16.2
unnamed: R22.2, U8.9
unnamed: D6.A, R23.2
unnamed: R25.1, R26.2, U8.8
unnamed: J10.A6, J10.B6, U10.3
unnamed: J10.A7, J10.B7, U10.5
unnamed: R28.2, USB1.1
unnamed: C18.2, U9.18, Y2.P$2
unnamed: C17.2, U9.19, Y2.P$1
unnamed: CHG1.2, U6.5
unnamed: CHG1.1, R31.1
unnamed: CHG1.3, R19.2
unnamed: GPIO18PU1.2, R32.1
unnamed: Q6.5, R36.2
unnamed: Q6.2, R37.2
unnamed: D8.A, R34.2
unnamed: R38.2, U13.9
unnamed: D9.A, R39.2
unnamed: R41.1, R42.2, U13.8
unnamed: J16.A6, J16.B6, U15.3
unnamed: J16.A7, J16.B7, U15.5
unnamed: R44.2, USB2.1
unnamed: C29.2, U14.18, Y3.P$2
unnamed: C28.2, U14.19, Y3.P$1
unnamed: CHG2.2, U11.5
unnamed: CHG2.1, R47.1
unnamed: CHG2.3, R35.2
unnamed: GPIO18PU2.2, R48.1
unnamed: Q8.5, R52.2
unnamed: Q8.2, R53.2
unnamed: D11.A, R50.2
unnamed: R54.2, U18.9
unnamed: D12.A, R55.2
unnamed: R57.1, R58.2, U18.8
unnamed: J22.A6, J22.B6, U20.3
unnamed: J22.A7, J22.B7, U20.5
unnamed: R60.2, USB3.1
unnamed: C39.2, U19.18, Y4.P$2
unnamed: C38.2, U19.19, Y4.P$1
unnamed: CHG3.2, U16.5
unnamed: CHG3.1, R63.1
unnamed: CHG3.3, R51.2
unnamed: GPIO18PU3.2, R64.1
unnamed: Q10.5, R68.2
unnamed: Q10.2, R69.2
unnamed: D14.A, R66.2
unnamed: R70.2, U23.9
unnamed: D15.A, R71.2
unnamed: R73.1, R74.2, U23.8
unnamed: J28.A6, J28.B6, U25.3
unnamed: J28.A7, J28.B7, U25.5
unnamed: R76.2, USB4.1
unnamed: C49.2, U24.18, Y5.P$2
unnamed: C48.2, U24.19, Y5.P$1
unnamed: CHG4.2, U21.5
unnamed: CHG4.1, R79.1
unnamed: CHG4.3, R67.2
unnamed: GPIO18PU4.2, R80.1
unnamed: Q12.5, R84.2
unnamed: Q12.2, R85.2
unnamed: D17.A, R82.2
unnamed: R86.2, U28.9
unnamed: D18.A, R87.2
unnamed: R89.1, R90.2, U28.8
unnamed: J34.A6, J34.B6, U30.3
unnamed: J34.A7, J34.B7, U30.5
unnamed: R92.2, USB5.1
unnamed: C59.2, U29.18, Y6.P$2
unnamed: C58.2, U29.19, Y6.P$1
unnamed: CHG5.2, U26.5
unnamed: CHG5.1, R95.1
unnamed: CHG5.3, R83.2
unnamed: GPIO18PU5.2, R96.1
unnamed: Q14.5, R100.2
unnamed: Q14.2, R101.2
unnamed: D20.A, R98.2
unnamed: R102.2, U33.9
unnamed: D21.A, R103.2
unnamed: R105.1, R106.2, U33.8
unnamed: J40.A6, J40.B6, U35.3
unnamed: J40.A7, J40.B7, U35.5
unnamed: R108.2, USB6.1
unnamed: C69.2, U34.18, Y7.P$2
unnamed: C68.2, U34.19, Y7.P$1
unnamed: CHG6.2, U31.5
unnamed: CHG6.1, R111.1
unnamed: CHG6.3, R99.2
unnamed: GPIO18PU6.2, R112.1
unnamed: Q16.5, R116.2
unnamed: Q16.2, R117.2
unnamed: D23.A, R114.2
unnamed: R118.2, U38.9
unnamed: D24.A, R119.2
unnamed: R121.1, R122.2, U38.8
unnamed: J46.A6, J46.B6, U40.3
unnamed: J46.A7, J46.B7, U40.5
unnamed: R124.2, USB7.1
unnamed: C79.2, U39.18, Y8.P$2
unnamed: C78.2, U39.19, Y8.P$1
unnamed: CHG7.2, U36.5
unnamed: CHG7.1, R127.1
unnamed: CHG7.3, R115.2
unnamed: GPIO18PU7.2, R128.1
unnamed: Q18.5, R132.2
unnamed: Q18.2, R133.2
unnamed: D26.A, R130.2
unnamed: R134.2, U43.9
unnamed: D27.A, R135.2
unnamed: R137.1, R138.2, U43.8
unnamed: J52.A6, J52.B6, U45.3
unnamed: J52.A7, J52.B7, U45.5
unnamed: R140.2, USB8.1
unnamed: C89.2, U44.18, Y9.P$2
unnamed: C88.2, U44.19, Y9.P$1
unnamed: CHG8.2, U41.5
unnamed: CHG8.1, R143.1
unnamed: CHG8.3, R131.2
unnamed: GPIO18PU8.2, R144.1
unnamed: Q20.5, R148.2
unnamed: Q20.2, R149.2
unnamed: D29.A, R146.2
unnamed: R150.2, U48.9
unnamed: D30.A, R151.2
unnamed: R153.1, R154.2, U48.8
unnamed: J58.A6, J58.B6, U50.3
unnamed: J58.A7, J58.B7, U50.5
unnamed: R156.2, USB9.1
unnamed: C99.2, U49.18, Y10.P$2
unnamed: C98.2, U49.19, Y10.P$1
unnamed: CHG9.2, U46.5
unnamed: CHG9.1, R159.1
unnamed: CHG9.3, R147.2
unnamed: GPIO18PU9.2, R160.1
RTS: Q2.4, R18.1, U2.19
RTS1: Q4.4, R21.1, U8.19
RTS2: Q6.4, R37.1, U13.19
RTS3: Q8.4, R53.1, U18.19
RTS4: Q10.4, R69.1, U23.19
RTS5: Q12.4, R85.1, U28.19
RTS6: Q14.4, R101.1, U33.19
RTS7: Q16.4, R117.1, U38.19
RTS8: Q18.4, R133.1, U43.19
RTS9: Q20.4, R149.1, U48.19
RX0: J7.5, U1.38, U2.21
RX1: J12.5, U8.21, U9.38
RX2: J18.5, U13.21, U14.38
RX3: J24.5, U18.21, U19.38
RX4: J30.5, U23.21, U24.38
RX5: J36.5, U28.21, U29.38
RX6: J42.5, U33.21, U34.38
RX7: J48.5, U38.21, U39.38
RX8: J54.5, U43.21, U44.38
RX9: J60.5, U48.21, U49.38
SCK: J4.11, U1.30
SCK1: J9.11, U9.30
SCK2: J15.11, U14.30
SCK3: J21.11, U19.30
SCK4: J27.11, U24.30
SCK5: J33.11, U29.30
SCK6: J39.11, U34.30
SCK7: J45.11, U39.30
SCK8: J51.11, U44.30
SCK9: J57.11, U49.30
SCL: J2.11, J3.4, U1.5
SCL1: J1.4, J8.11, U9.5
SCL2: J13.4, J14.11, U14.5
SCL3: J19.4, J20.11, U19.5
SCL4: J25.4, J26.11, U24.5
SCL5: J31.4, J32.11, U29.5
SCL6: J37.4, J38.11, U34.5
SCL7: J43.4, J44.11, U39.5
SCL8: J49.4, J50.11, U44.5
SCL9: J55.4, J56.11, U49.5
SDA: J2.12, J3.3, U1.4
SDA1: J1.3, J8.12, U9.4
SDA2: J13.3, J14.12, U14.4
SDA3: J19.3, J20.12, U19.4
SDA4: J25.3, J26.12, U24.4
SDA5: J31.3, J32.12, U29.4
SDA6: J37.3, J38.12, U34.4
SDA7: J43.3, J44.12, U39.4
SDA8: J49.3, J50.12, U44.4
SDA9: J55.3, J56.12, U49.4
TX0: J7.6, U1.37, U2.20
TX1: J12.6, U8.20, U9.37
TX2: J18.6, U13.20, U14.37
TX3: J24.6, U18.20, U19.37
TX4: J30.6, U23.20, U24.37
TX5: J36.6, U28.20, U29.37
TX6: J42.6, U33.20, U34.37
TX7: J48.6, U38.20, U39.37
TX8: J54.6, U43.20, U44.37
TX9: J60.6, U48.20, U49.37
USB_SEL: U5.10, USB.2
USB_SEL1: U10.10, USB1.2
USB_SEL2: U15.10, USB2.2
USB_SEL3: U20.10, USB3.2
USB_SEL4: U25.10, USB4.2
USB_SEL5: U30.10, USB5.2
USB_SEL6: U35.10, USB6.2
USB_SEL7: U40.10, USB7.2
USB_SEL8: U45.10, USB8.2
USB_SEL9: U50.10, USB9.2
VIN: C7.1, D2.C, Q1.2, R8.1, U3.1
VIN1: C9.1, D4.C, Q3.2, R24.1, U7.1
VIN2: C21.1, D7.C, Q5.2, R40.1, U12.1
VIN3: C31.1, D10.C, Q7.2, R56.1, U17.1
VIN4: C41.1, D13.C, Q9.2, R72.1, U22.1
VIN5: C51.1, D16.C, Q11.2, R88.1, U27.1
VIN6: C61.1, D19.C, Q13.2, R104.1, U32.1
VIN7: C71.1, D22.C, Q15.2, R120.1, U37.1
VIN8: C81.1, D25.C, Q17.2, R136.1, U42.1
VIN9: C91.1, D28.C, Q19.2, R152.1, U47.1
V_BATT: C6.1, J2.1, JP2.2, Q1.3, U4.3
V_BATT1: C12.1, J8.1, JP1.2, Q3.3, U6.3
V_BATT2: C23.1, J14.1, JP3.2, Q5.3, U11.3
V_BATT3: C33.1, J20.1, JP4.2, Q7.3, U16.3
V_BATT4: C43.1, J26.1, JP5.2, Q9.3, U21.3
V_BATT5: C53.1, J32.1, JP6.2, Q11.3, U26.3
V_BATT6: C63.1, J38.1, JP7.2, Q13.3, U31.3
V_BATT7: C73.1, J44.1, JP8.2, Q15.3, U36.3
V_BATT8: C83.1, J50.1, JP9.2, Q17.3, U41.3
V_BATT9: C93.1, J56.1, JP10.2, Q19.3, U46.3
V_USB: C19.1, D2.A, J2.3, J5.VBUS1, J5.VBUS2, Q1.1, R3.1, R5.2, R7.2, U4.4
V_USB1: C13.1, D4.A, J8.3, J10.VBUS1, J10.VBUS2, Q3.1, R15.2, R16.1, R25.2, U6.4
V_USB2: C24.1, D7.A, J14.3, J16.VBUS1, J16.VBUS2, Q5.1, R33.2, R34.1, R41.2, U11.4
V_USB3: C34.1, D10.A, J20.3, J22.VBUS1, J22.VBUS2, Q7.1, R49.2, R50.1, R57.2, U16.4
V_USB4: C44.1, D13.A, J26.3, J28.VBUS1, J28.VBUS2, Q9.1, R65.2, R66.1, R73.2, U21.4
V_USB5: C54.1, D16.A, J32.3, J34.VBUS1, J34.VBUS2, Q11.1, R81.2, R82.1, R89.2, U26.4
V_USB6: C64.1, D19.A, J38.3, J40.VBUS1, J40.VBUS2, Q13.1, R97.2, R98.1, R105.2, U31.4
V_USB7: C74.1, D22.A, J44.3, J46.VBUS1, J46.VBUS2, Q15.1, R113.2, R114.1, R121.2, U36.4
V_USB8: C84.1, D25.A, J50.3, J52.VBUS1, J52.VBUS2, Q17.1, R129.2, R130.1, R137.2, U41.4
V_USB9: C94.1, D28.A, J56.3, J58.VBUS1, J58.VBUS2, Q19.1, R145.2, R146.1, R153.2, U46.4

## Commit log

2020-12-01 power routing looking almost there
2020-12-02 added charge current jumper options and did a bunch of routing
2020-12-04 Moved to smaller/newer 32.768kHz crystal
2020-12-04 moving vreg in progress
2020-12-07 All IO (except "extra SMD IO") routed
2020-12-07 routing "done"
2020-12-08 DRC errors - some little nudging
2020-12-09 schematic cleanup and added recommended RC (cap to GND) on enable pin
2020-12-09 "0" boot test point moved to 50 mil grid
2020-12-09 added JTAG test points
2020-12-09 trestrict on cp210x and ground trace connection from outer pad to EPAD
2020-12-09 Measures updated
2020-12-09 nudging vias to avoid silk
2020-12-10 prod_ids for module and usb switch ic
2020-12-11 corrected extra IO sch note, moved "0" button to align with reset.
2020-12-11 Group design review changes - USB switch to jumper and much more!
    -Moved USB selection switch to a 3-way jumper on the bottom.
    -Increased Battery + and - label text size
    -switched 5.1K resistors to 0402 package
    -Moved Charge LED away from standoff
    -More GND vias under CP210X
    -More GND vias near GND pad on JST batt input
2020-12-14 Final changes from groupd proto review (library work)
    -Added tNames and tValues to TC7 USB switch IC.
    -repositioned tNames and tValues on CP210X footprint.
2020-12-14 Moved to new DRU, then moved some stuff for better gnd flow
    -note, manually kept gnd pour poly isolates at 7/10/10/7, to avoid exposing mask on square pad cornder masks.
2020-12-14 eng run checklist
    -one proportional font in sch fixed.
    -updated auto-reset paragraph in sch to reflect S2 strapping pins
    -updated USB selection jumper paragraph to more clearly show options and default.
    -removed S2 Module dimensions from footprint (forgot about them while doing the library work early on)
    -added more dimensions for header rows
2020-12-15 DRU settings: mask openings to 2.5mil
2020-12-15 Added measures for JTAG header
    -also created dimensional drawings in PDF/PNG
2020-12-15 v01 proto gerbers
2021-02-15 v10
    -switched to normally open jumper on GPIO18. Testing showed this was unnecessary. (also updated jumper paragraph in schematic).
    -bumped version to v10 in both sch and brd.
2021-02-15 datasheet page correction in sch note about GPIO18 jumper
2021-02-17 Reds Review changes - nudged test points
    -Test points were too close to bottom SMD header pads. Moved them slightly away.
    -Fixed one DRC angle error on a trace off of jumper pad
    -Changes EN and RESET buzzard bottom labels to be POINTER END as input to board.
2021-02-18 Adjusted GPIO45 and 46 to be INPUT pointer style labels
2021-02-18 cleaning up measures
2021-02-18 update measures PDF and PNG files
2021-02-25 Panel brd and gerbers for v10
2021-03-22 BOM switch - momentary switches to new nicer button (SWCH-15606)
    Note, I also updated production panel file, so this should help when using this to create recipe on pnp machine.
2021-03-31 image link update
2021-04-05 Clarifying which datasheet to reference about GPIO18 pullup
2021-04-05 GPIO18 paragraph DS page correction (PG 20)
2021-04-08 Update README.md
    Fix links and information
